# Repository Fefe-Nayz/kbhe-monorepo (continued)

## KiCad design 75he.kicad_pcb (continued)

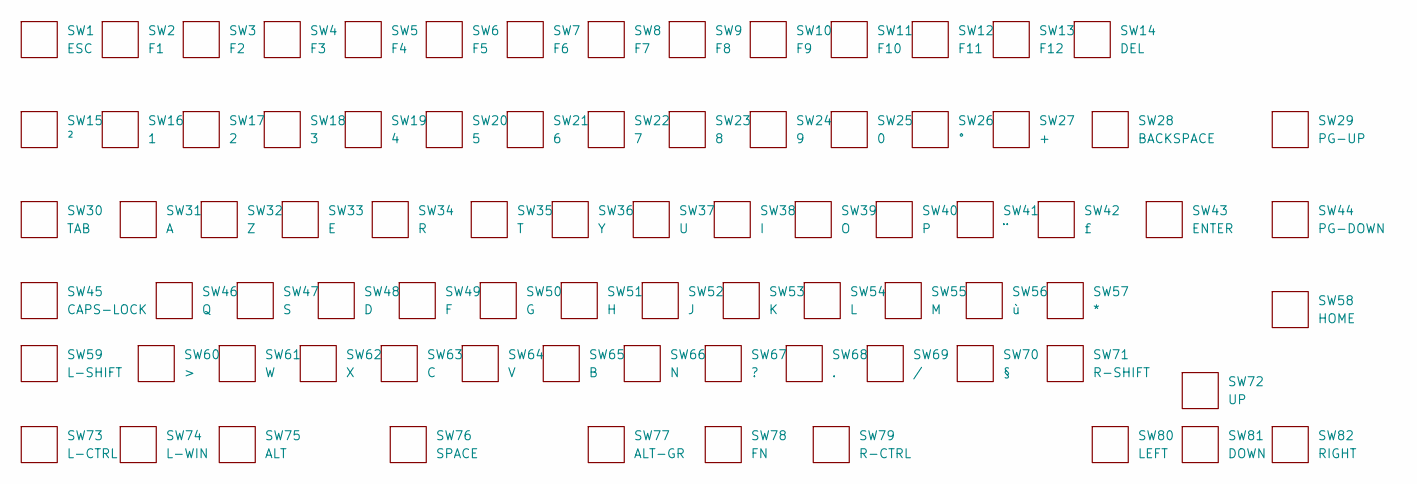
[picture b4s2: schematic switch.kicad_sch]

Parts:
SW1: ESC; Switch_1U
SW2: F1; Switch_1U
SW3: F2; Switch_1U
SW4: F3; Switch_1U
SW5: F4; Switch_1U
SW6: F5; Switch_1U
SW7: F6; Switch_1U
SW8: F7; Switch_1U
SW9: F8; Switch_1U
SW10: F9; Switch_1U
SW11: F10; Switch_1U
SW12: F11; Switch_1U
SW13: F12; Switch_1U
SW14: DEL; Switch_1U
SW15: ²; Switch_1U
SW16: 1; Switch_1U
SW17: 2; Switch_1U
SW18: 3; Switch_1U
SW19: 4; Switch_1U
SW20: 5; Switch_1U
SW21: 6; Switch_1U
SW22: 7; Switch_1U
SW23: 8; Switch_1U
SW24: 9; Switch_1U
SW25: 0; Switch_1U
SW26: °; Switch_1U
SW27: +; Switch_1U
SW28: BACKSPACE; Switch_2U
SW29: PG-UP; Switch_1U
SW30: TAB; Switch_1.5U
SW31: A; Switch_1U
SW32: Z; Switch_1U
SW33: E; Switch_1U
SW34: R; Switch_1U
SW35: T; Switch_1U
SW36: Y; Switch_1U
SW37: U; Switch_1U
SW38: I; Switch_1U
SW39: O; Switch_1U
SW40: P; Switch_1U
SW41: ¨; Switch_1U
SW42: £; Switch_1U
SW43: ENTER; Switch_ENTER_ISO
SW44: PG-DOWN; Switch_1U
SW45: CAPS-LOCK; Switch_1.75U
SW46: Q; Switch_1U
SW47: S; Switch_1U
SW48: D; Switch_1U
SW49: F; Switch_1U
SW50: G; Switch_1U
SW51: H; Switch_1U
SW52: J; Switch_1U
SW53: K; Switch_1U
SW54: L; Switch_1U
SW55: M; Switch_1U
SW56: ù; Switch_1U
SW57: *; Switch_1U
SW58: HOME; Switch_1U
SW59: L-SHIFT; Switch_1.25U
SW60: >; Switch_1U
SW61: W; Switch_1U
SW62: X; Switch_1U
SW63: C; Switch_1U
SW64: V; Switch_1U
SW65: B; Switch_1U
SW66: N; Switch_1U
SW67: ?; Switch_1U
SW68: .; Switch_1U
SW69: /; Switch_1U
SW70: §; Switch_1U
SW71: R-SHIFT; Switch_1.75U
SW72: UP; Switch_1U
SW73: L-CTRL; Switch_1.25U
SW74: L-WIN; Switch_1.25U
SW75: ALT; Switch_1.25U
SW76: SPACE; Switch_6.25U
SW77: ALT-GR; Switch_1U
SW78: FN; Switch_1U
SW79: R-CTRL; Switch_1U
SW80: LEFT; Switch_1U
SW81: DOWN; Switch_1U
SW82: RIGHT; Switch_1U

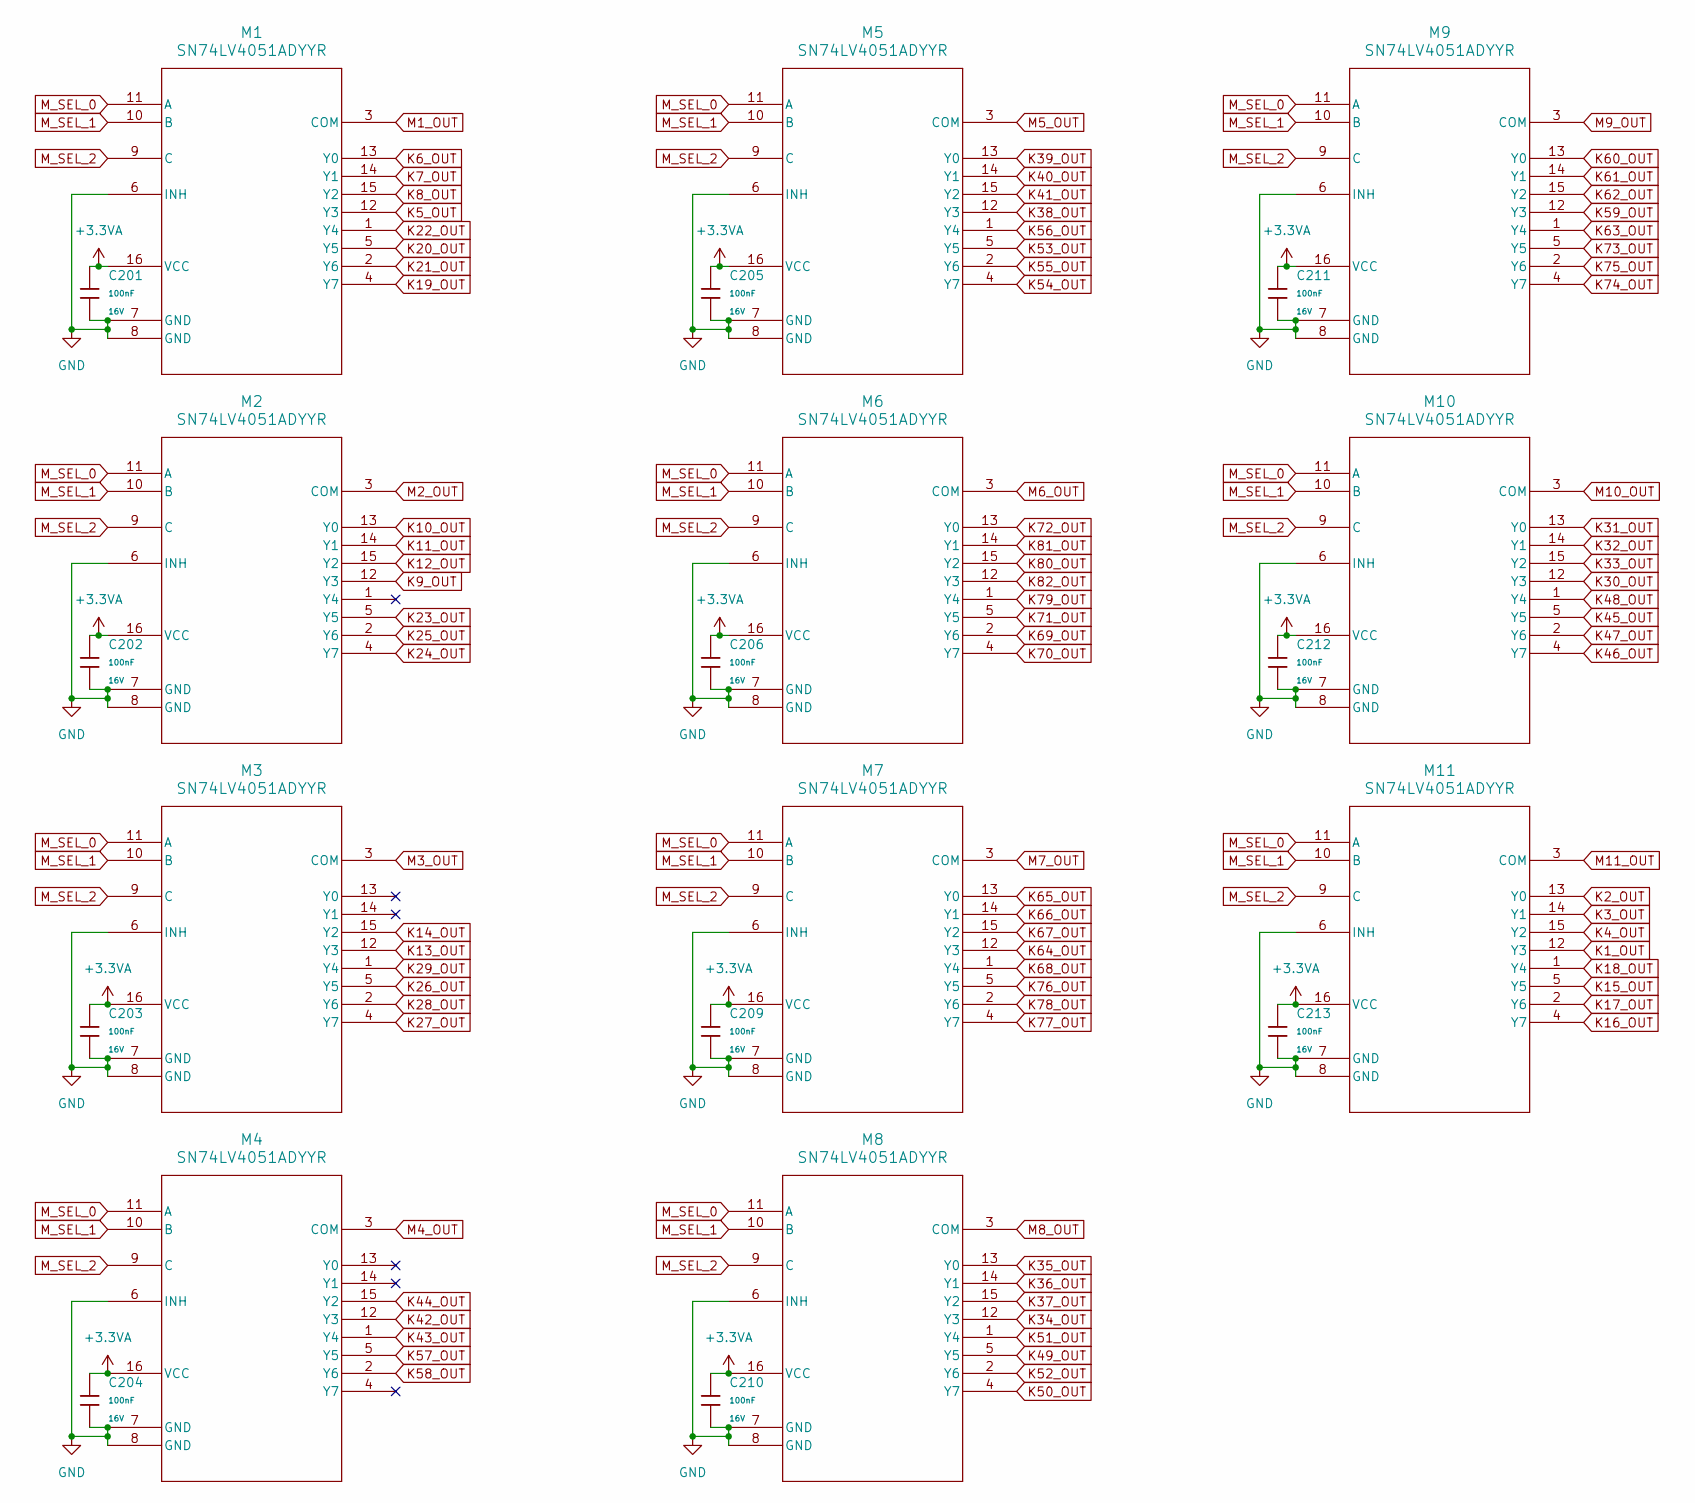
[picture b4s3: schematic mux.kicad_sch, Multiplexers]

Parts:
C201, C202, C203, C204, C205, C206, C209, C210, C211, C212, C213: 100nF; C_0402; Voltage Rated 16V; Tolerance ±10%; Part CL05B104KO5NNNC; LCSC C1525
M1, M2, M3, M4, M5, M6, M7, M8, M9, M10, M11: SN74LV4051ADYYR; SOT-23-THIN16_DYY_TEX

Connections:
+3.3VA: C201.1, C202.1, C203.1, C204.1, C205.1, C206.1, C209.1, C210.1, C211.1, C212.1, C213.1, M1.16 (VCC), M2.16 (VCC), M3.16 (VCC), M4.16 (VCC), M5.16 (VCC), M6.16 (VCC), M7.16 (VCC), M8.16 (VCC), M9.16 (VCC), M10.16 (VCC), M11.16 (VCC); also elsewhere on the board
GND: C201.2, C202.2, C203.2, C204.2, C205.2, C206.2, C209.2, C210.2, C211.2, C212.2, C213.2, M1.6 (INH), M1.7 (GND), M1.8 (GND), M2.6 (INH), M2.7 (GND), M2.8 (GND), M3.6 (INH), M3.7 (GND), M3.8 (GND), M4.6 (INH), M4.7 (GND), M4.8 (GND), M5.6 (INH), M5.7 (GND), M5.8 (GND), M6.6 (INH), M6.7 (GND), M6.8 (GND), M7.6 (INH), M7.7 (GND), M7.8 (GND), M8.6 (INH), M8.7 (GND), M8.8 (GND), M9.6 (INH), M9.7 (GND), M9.8 (GND), M10.6 (INH), M10.7 (GND), M10.8 (GND), M11.6 (INH), M11.7 (GND), M11.8 (GND); also elsewhere on the board
K1_OUT: M11.12 (Y3); also elsewhere on the board
K2_OUT: M11.13 (Y0); also elsewhere on the board
K3_OUT: M11.14 (Y1); also elsewhere on the board
K4_OUT: M11.15 (Y2); also elsewhere on the board
K5_OUT: M1.12 (Y3); also elsewhere on the board
K6_OUT: M1.13 (Y0); also elsewhere on the board
K7_OUT: M1.14 (Y1); also elsewhere on the board
K8_OUT: M1.15 (Y2); also elsewhere on the board
K9_OUT: M2.12 (Y3); also elsewhere on the board
K10_OUT: M2.13 (Y0); also elsewhere on the board
K11_OUT: M2.14 (Y1); also elsewhere on the board
K12_OUT: M2.15 (Y2); also elsewhere on the board
K13_OUT: M3.12 (Y3); also elsewhere on the board
K14_OUT: M3.15 (Y2); also elsewhere on the board
K15_OUT: M11.5 (Y5); also elsewhere on the board
K16_OUT: M11.4 (Y7); also elsewhere on the board
K17_OUT: M11.2 (Y6); also elsewhere on the board
K18_OUT: M11.1 (Y4); also elsewhere on the board
K19_OUT: M1.4 (Y7); also elsewhere on the board
K20_OUT: M1.5 (Y5); also elsewhere on the board
K21_OUT: M1.2 (Y6); also elsewhere on the board
K22_OUT: M1.1 (Y4); also elsewhere on the board
K23_OUT: M2.5 (Y5); also elsewhere on the board
K24_OUT: M2.4 (Y7); also elsewhere on the board
K25_OUT: M2.2 (Y6); also elsewhere on the board
K26_OUT: M3.5 (Y5); also elsewhere on the board
K27_OUT: M3.4 (Y7); also elsewhere on the board
K28_OUT: M3.2 (Y6); also elsewhere on the board
K29_OUT: M3.1 (Y4); also elsewhere on the board
K30_OUT: M10.12 (Y3); also elsewhere on the board
K31_OUT: M10.13 (Y0); also elsewhere on the board
K32_OUT: M10.14 (Y1); also elsewhere on the board
K33_OUT: M10.15 (Y2); also elsewhere on the board
K34_OUT: M8.12 (Y3); also elsewhere on the board
K35_OUT: M8.13 (Y0); also elsewhere on the board
K36_OUT: M8.14 (Y1); also elsewhere on the board
K37_OUT: M8.15 (Y2); also elsewhere on the board
K38_OUT: M5.12 (Y3); also elsewhere on the board
K39_OUT: M5.13 (Y0); also elsewhere on the board
K40_OUT: M5.14 (Y1); also elsewhere on the board
K41_OUT: M5.15 (Y2); also elsewhere on the board
K42_OUT: M4.12 (Y3); also elsewhere on the board
K43_OUT: M4.1 (Y4); also elsewhere on the board
K44_OUT: M4.15 (Y2); also elsewhere on the board
K45_OUT: M10.5 (Y5); also elsewhere on the board
K46_OUT: M10.4 (Y7); also elsewhere on the board
K47_OUT: M10.2 (Y6); also elsewhere on the board
K48_OUT: M10.1 (Y4); also elsewhere on the board
K49_OUT: M8.5 (Y5); also elsewhere on the board
K50_OUT: M8.4 (Y7); also elsewhere on the board
K51_OUT: M8.1 (Y4); also elsewhere on the board
K52_OUT: M8.2 (Y6); also elsewhere on the board
K53_OUT: M5.5 (Y5); also elsewhere on the board
K54_OUT: M5.4 (Y7); also elsewhere on the board
K55_OUT: M5.2 (Y6); also elsewhere on the board
K56_OUT: M5.1 (Y4); also elsewhere on the board
K57_OUT: M4.5 (Y5); also elsewhere on the board
K58_OUT: M4.2 (Y6); also elsewhere on the board
K59_OUT: M9.12 (Y3); also elsewhere on the board
K60_OUT: M9.13 (Y0); also elsewhere on the board
K61_OUT: M9.14 (Y1); also elsewhere on the board
K62_OUT: M9.15 (Y2); also elsewhere on the board
K63_OUT: M9.1 (Y4); also elsewhere on the board
K64_OUT: M7.12 (Y3); also elsewhere on the board
K65_OUT: M7.13 (Y0); also elsewhere on the board
K66_OUT: M7.14 (Y1); also elsewhere on the board
K67_OUT: M7.15 (Y2); also elsewhere on the board
K68_OUT: M7.1 (Y4); also elsewhere on the board
K69_OUT: M6.2 (Y6); also elsewhere on the board
K70_OUT: M6.4 (Y7); also elsewhere on the board
K71_OUT: M6.5 (Y5); also elsewhere on the board
K72_OUT: M6.13 (Y0); also elsewhere on the board
K73_OUT: M9.5 (Y5); also elsewhere on the board
K74_OUT: M9.4 (Y7); also elsewhere on the board
K75_OUT: M9.2 (Y6); also elsewhere on the board
K76_OUT: M7.5 (Y5); also elsewhere on the board
K77_OUT: M7.4 (Y7); also elsewhere on the board
K78_OUT: M7.2 (Y6); also elsewhere on the board
K79_OUT: M6.1 (Y4); also elsewhere on the board
K80_OUT: M6.15 (Y2); also elsewhere on the board
K81_OUT: M6.14 (Y1); also elsewhere on the board
K82_OUT: M6.12 (Y3); also elsewhere on the board
M1_OUT: M1.3 (COM); also elsewhere on the board
M2_OUT: M2.3 (COM); also elsewhere on the board
M3_OUT: M3.3 (COM); also elsewhere on the board
M4_OUT: M4.3 (COM); also elsewhere on the board
M5_OUT: M5.3 (COM); also elsewhere on the board
M6_OUT: M6.3 (COM); also elsewhere on the board
M7_OUT: M7.3 (COM); also elsewhere on the board
M8_OUT: M8.3 (COM); also elsewhere on the board
M9_OUT: M9.3 (COM); also elsewhere on the board
M10_OUT: M10.3 (COM); also elsewhere on the board
M11_OUT: M11.3 (COM); also elsewhere on the board
M_SEL_0: M1.11 (A), M2.11 (A), M3.11 (A), M4.11 (A), M5.11 (A), M6.11 (A), M7.11 (A), M8.11 (A), M9.11 (A), M10.11 (A), M11.11 (A); also elsewhere on the board
M_SEL_1: M1.10 (B), M2.10 (B), M3.10 (B), M4.10 (B), M5.10 (B), M6.10 (B), M7.10 (B), M8.10 (B), M9.10 (B), M10.10 (B), M11.10 (B); also elsewhere on the board
M_SEL_2: M1.9 (C), M2.9 (C), M3.9 (C), M4.9 (C), M5.9 (C), M6.9 (C), M7.9 (C), M8.9 (C), M9.9 (C), M10.9 (C), M11.9 (C); also elsewhere on the board

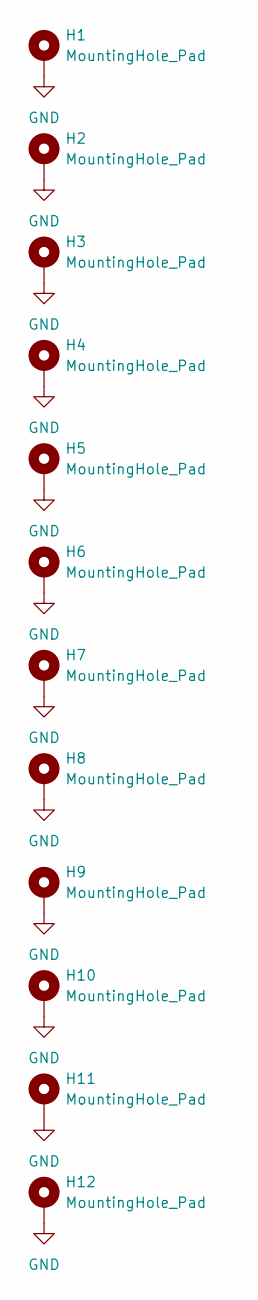
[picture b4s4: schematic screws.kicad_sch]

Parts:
H1, H2, H3, H4, H5, H6, H7, H8, H9, H10, H11, H12: MountingHole_Pad; MountingHole_2.2mm_M2_ISO14580_Pad

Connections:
GND: H1.1, H2.1, H3.1, H4.1, H5.1, H6.1, H7.1, H8.1, H9.1, H10.1, H11.1, H12.1; also elsewhere on the board

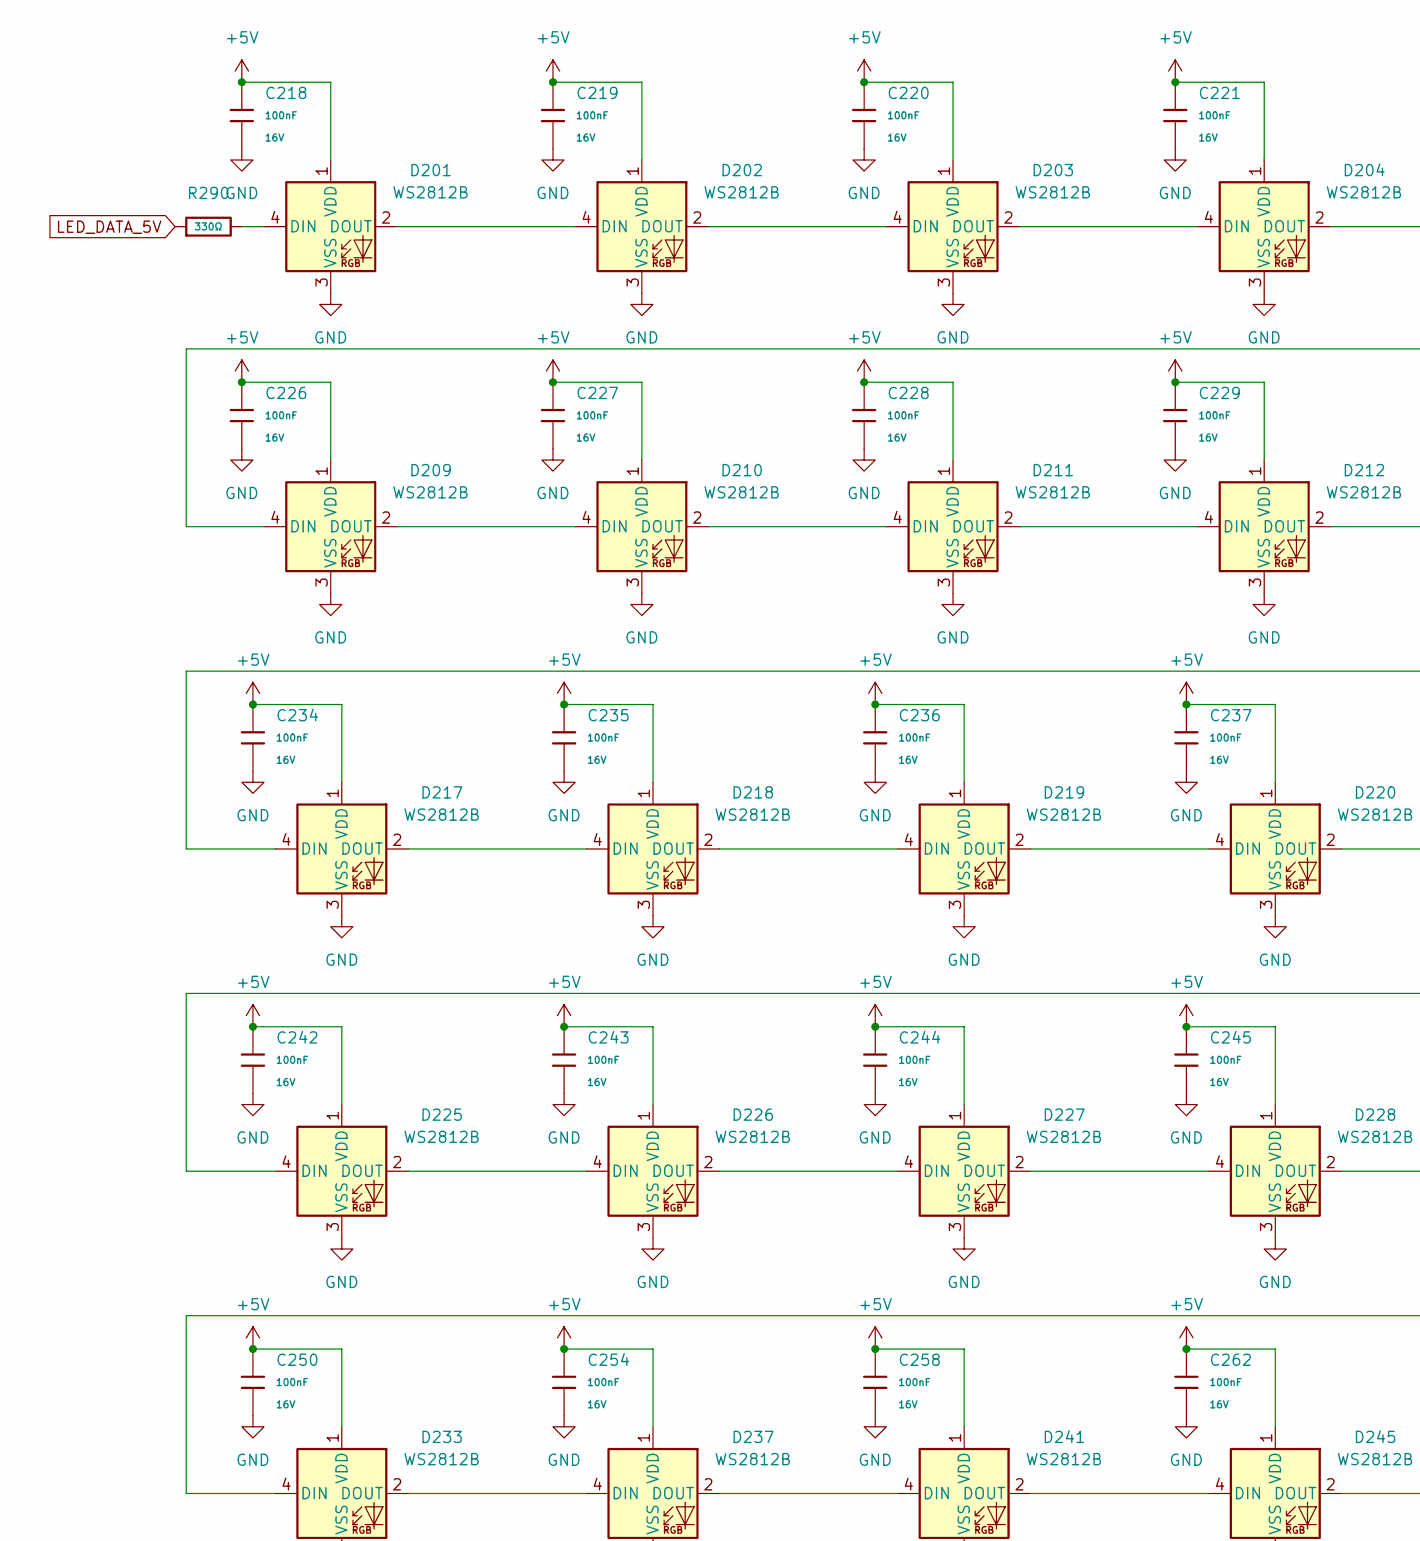
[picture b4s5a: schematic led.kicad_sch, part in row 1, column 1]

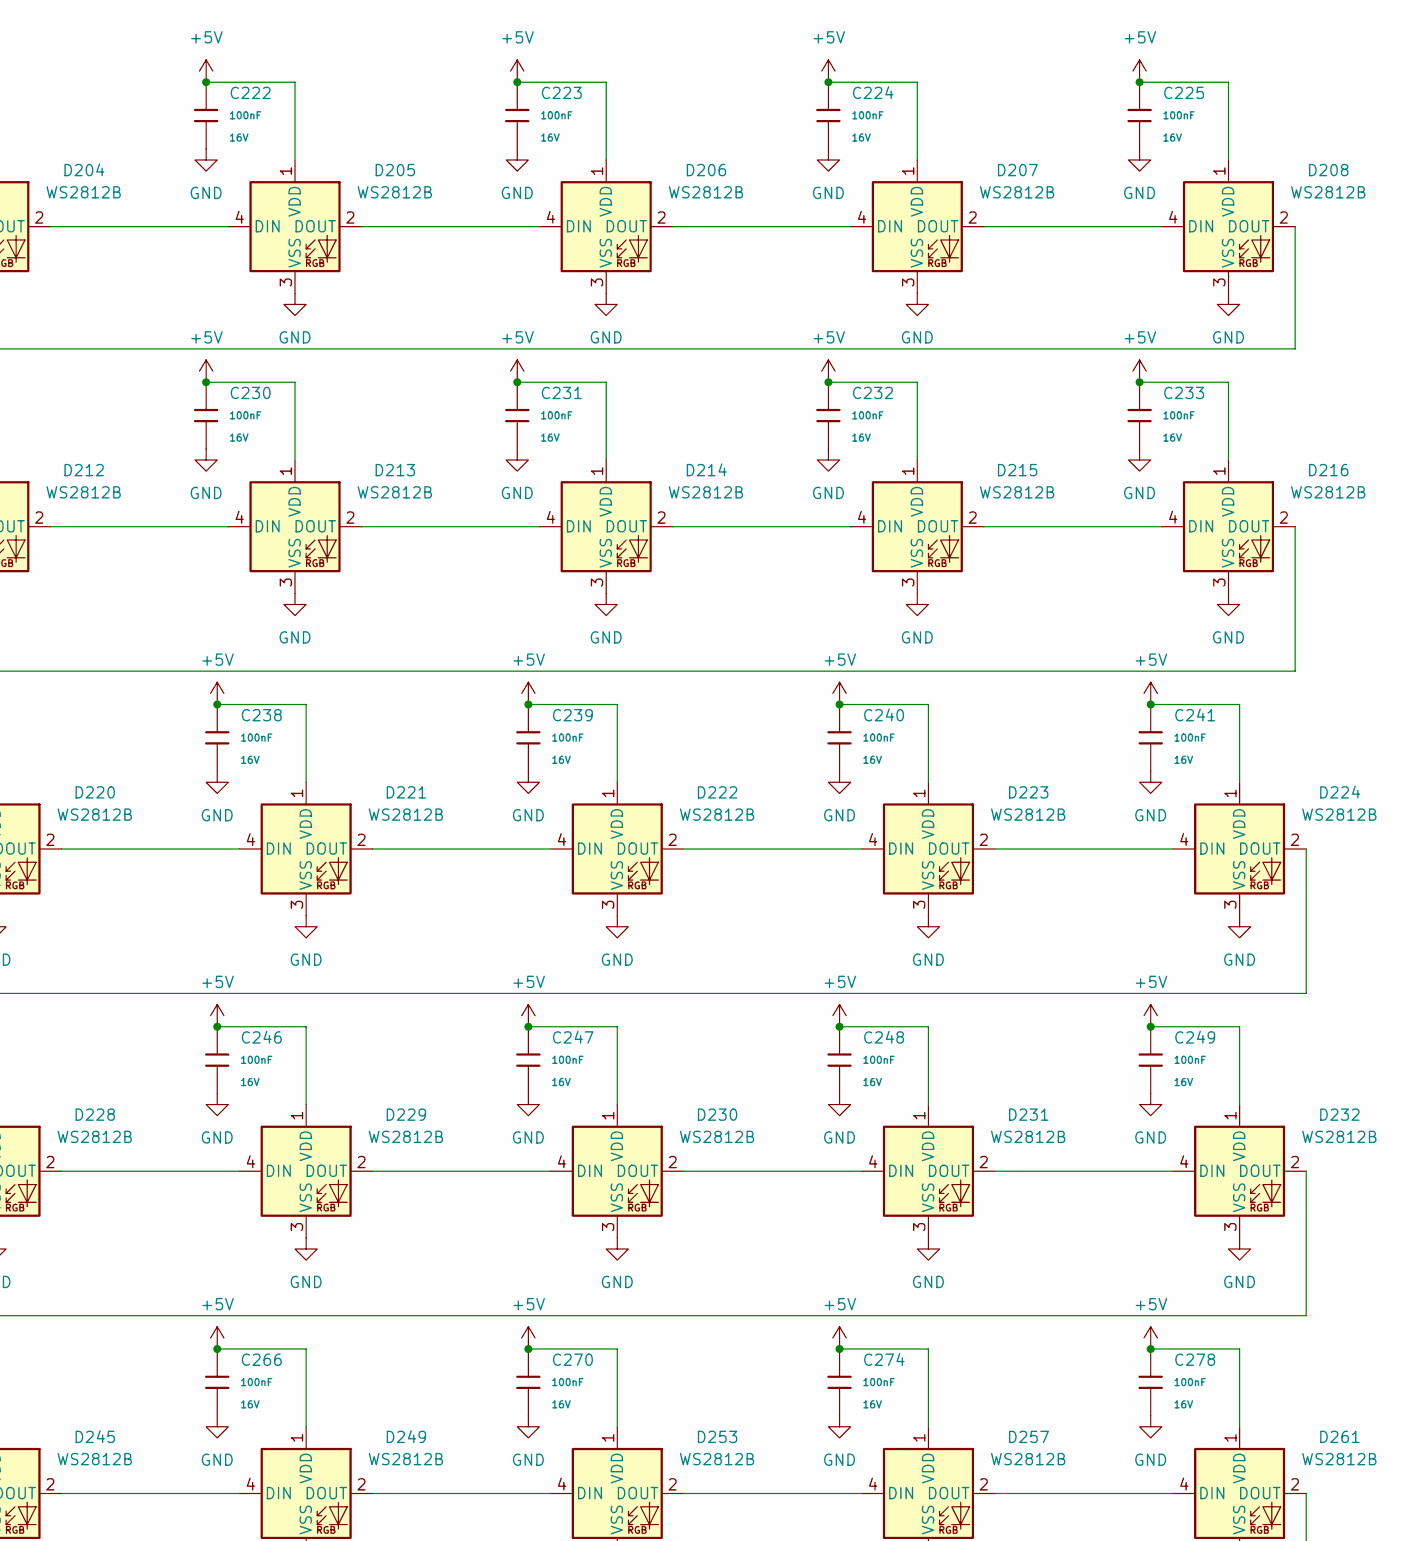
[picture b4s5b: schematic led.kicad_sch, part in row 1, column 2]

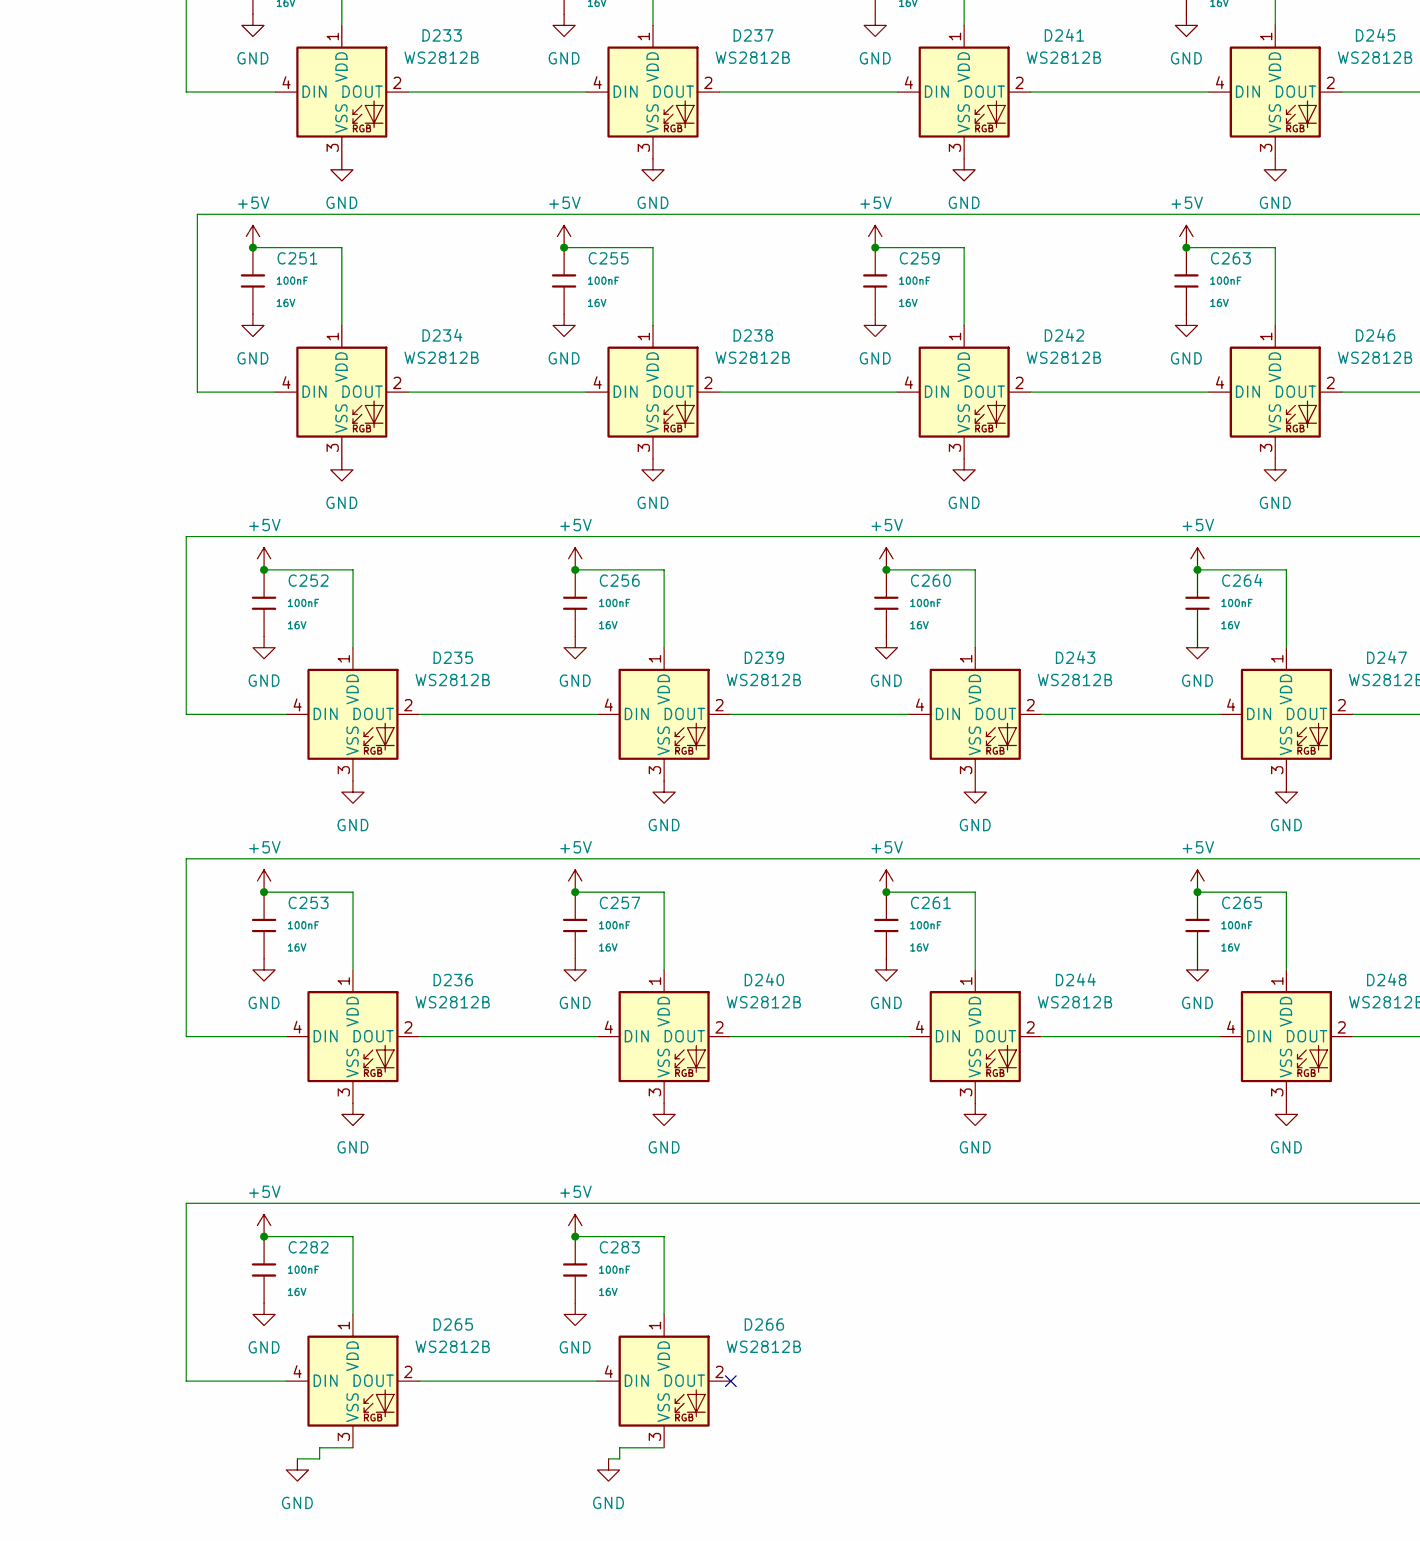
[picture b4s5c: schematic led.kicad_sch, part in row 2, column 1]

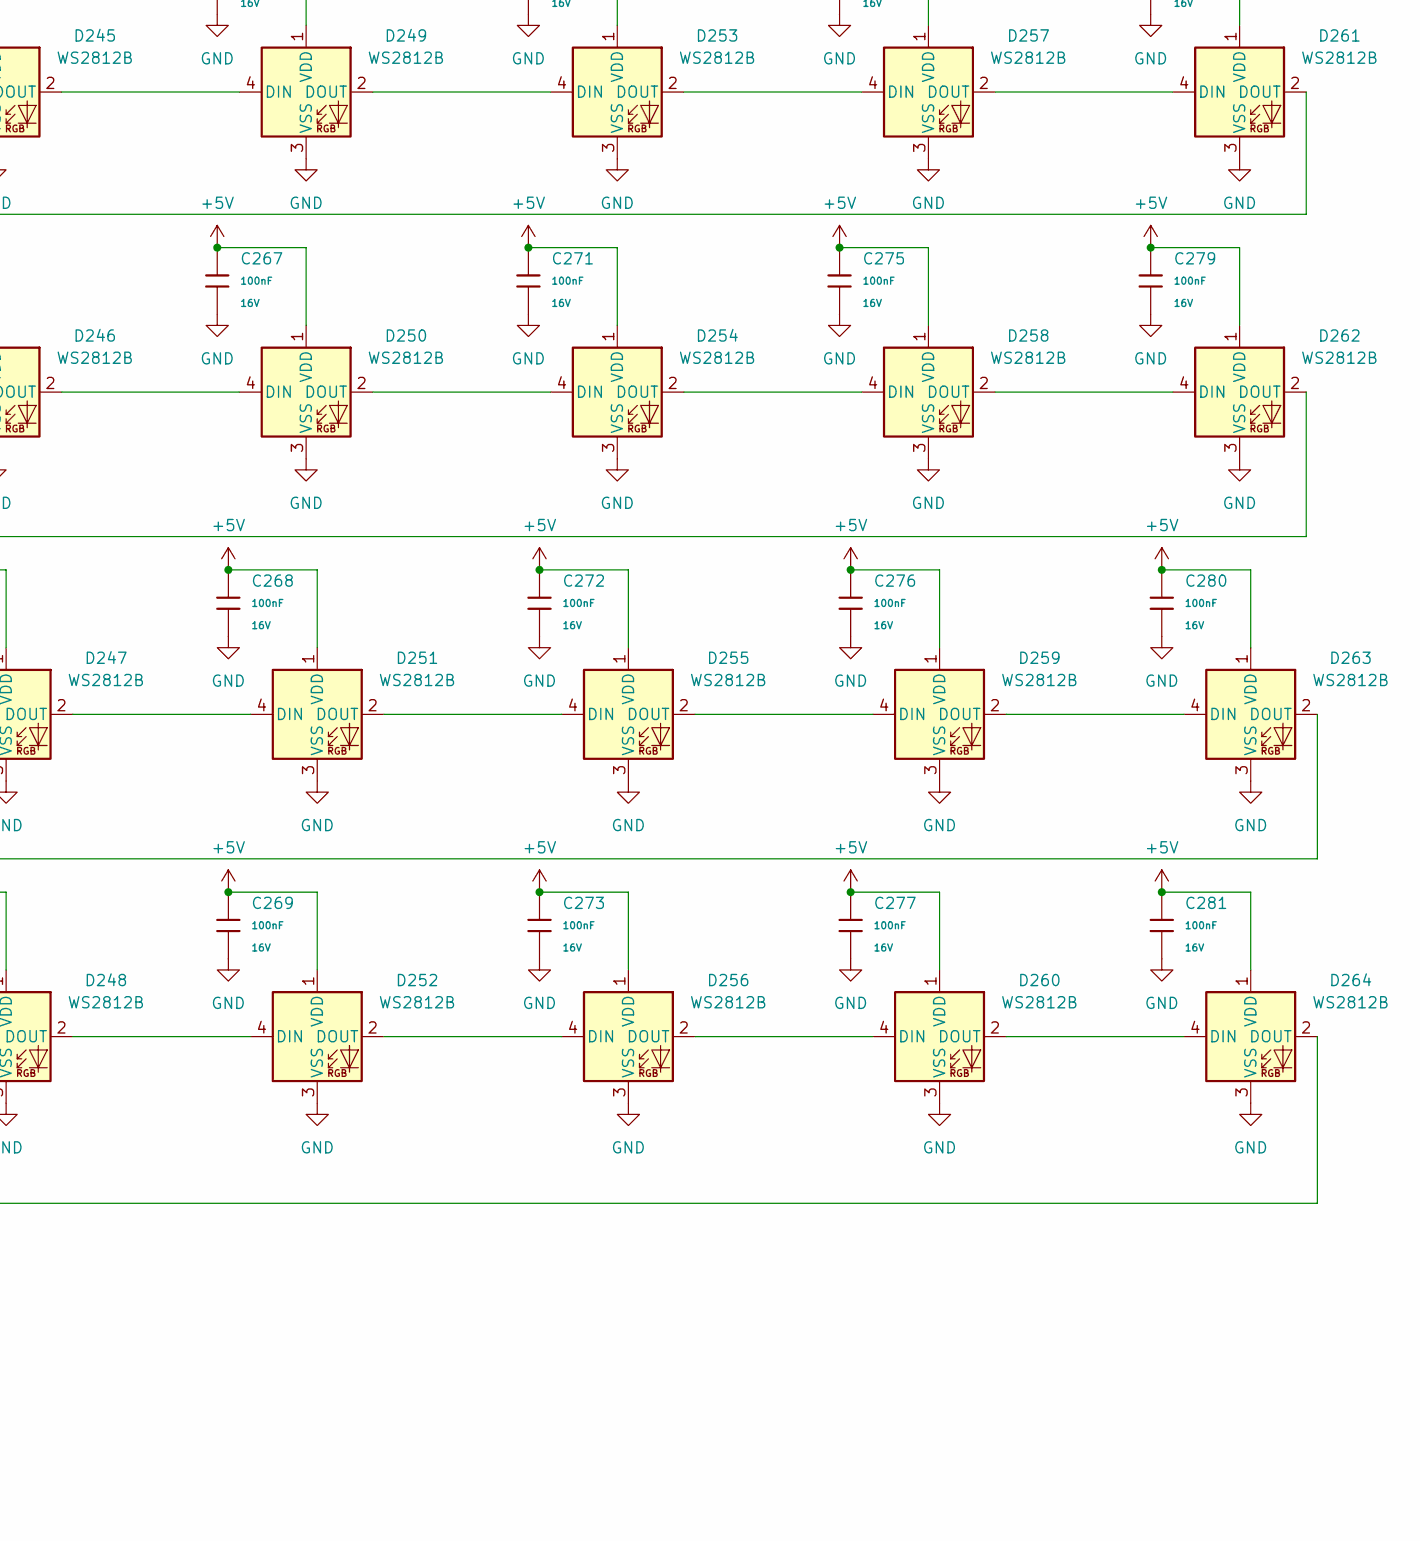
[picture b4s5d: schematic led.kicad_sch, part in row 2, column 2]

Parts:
C218, C219, C220, C221, C222, C223, C224, C225, C226, C227, C228, C229, C230, C231, C232, C233, C234, C235, C236, C237, C238, C239, C240, C241, C242, C243, C244, C245, C246, C247, C248, C249, C250, C251, C252, C253, C254, C255, C256, C257, C258, C259, C260, C261, C262, C263, C264, C265, C266, C267, C268, C269, C270, C271, C272, C273, C274, C275, C276, C277, C278, C279, C280, C281, C282, C283: 100nF; C_0402; Voltage Rated 16V; Tolerance ±10%; Part CL05B104KO5NNNC; LCSC C1525
D201, D202, D203, D204, D205, D206, D207, D208, D209, D210, D211, D212, D213, D214, D215, D216, D217, D218, D219, D220, D221, D222, D223, D224, D225, D226, D227, D228, D229, D230, D231, D232, D233, D234, D235, D236, D237, D238, D239, D240, D241, D242, D243, D244, D245, D246, D247, D248, D249, D250, D251, D252, D253, D254, D255, D256, D257, D258, D259, D260, D261, D262, D263, D264, D265, D266: WS2812B; LED_WS2812B_PLCC4_5.0x5.0mm_P3.2mm; LCSC C22461793
R290: 330Ω; R_0603; Overload Voltage (Max) 75V; Tolerance ±1%; Part 0603WAF3300T5E; LCSC C23138

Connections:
+5V: C218.1, C219.1, C220.1, C221.1, C222.1, C223.1, C224.1, C225.1, C226.1, C227.1, C228.1, C229.1, C230.1, C231.1, C232.1, C233.1, C234.1, C235.1, C236.1, C237.1, C238.1, C239.1, C240.1, C241.1, C242.1, C243.1, C244.1, C245.1, C246.1, C247.1, C248.1, C249.1, C250.1, C251.1, C252.1, C253.1, C254.1, C255.1, C256.1, C257.1, C258.1, C259.1, C260.1, C261.1, C262.1, C263.1, C264.1, C265.1, C266.1, C267.1, C268.1, C269.1, C270.1, C271.1, C272.1, C273.1, C274.1, C275.1, C276.1, C277.1, C278.1, C279.1, C280.1, C281.1, C282.1, C283.1, D201.1 (VDD), D202.1 (VDD), D203.1 (VDD), D204.1 (VDD), D205.1 (VDD), D206.1 (VDD), D207.1 (VDD), D208.1 (VDD), D209.1 (VDD), D210.1 (VDD), D211.1 (VDD), D212.1 (VDD), D213.1 (VDD), D214.1 (VDD), D215.1 (VDD), D216.1 (VDD), D217.1 (VDD), D218.1 (VDD), D219.1 (VDD), D220.1 (VDD), D221.1 (VDD), D222.1 (VDD), D223.1 (VDD), D224.1 (VDD), D225.1 (VDD), D226.1 (VDD), D227.1 (VDD), D228.1 (VDD), D229.1 (VDD), D230.1 (VDD), D231.1 (VDD), D232.1 (VDD), D233.1 (VDD), D234.1 (VDD), D235.1 (VDD), D236.1 (VDD), D237.1 (VDD), D238.1 (VDD), D239.1 (VDD), D240.1 (VDD), D241.1 (VDD), D242.1 (VDD), D243.1 (VDD), D244.1 (VDD), D245.1 (VDD), D246.1 (VDD), D247.1 (VDD), D248.1 (VDD), D249.1 (VDD), D250.1 (VDD), D251.1 (VDD), D252.1 (VDD), D253.1 (VDD), D254.1 (VDD), D255.1 (VDD), D256.1 (VDD), D257.1 (VDD), D258.1 (VDD), D259.1 (VDD), D260.1 (VDD), D261.1 (VDD), D262.1 (VDD), D263.1 (VDD), D264.1 (VDD), D265.1 (VDD), D266.1 (VDD); also elsewhere on the board
GND: C218.2, C219.2, C220.2, C221.2, C222.2, C223.2, C224.2, C225.2, C226.2, C227.2, C228.2, C229.2, C230.2, C231.2, C232.2, C233.2, C234.2, C235.2, C236.2, C237.2, C238.2, C239.2, C240.2, C241.2, C242.2, C243.2, C244.2, C245.2, C246.2, C247.2, C248.2, C249.2, C250.2, C251.2, C252.2, C253.2, C254.2, C255.2, C256.2, C257.2, C258.2, C259.2, C260.2, C261.2, C262.2, C263.2, C264.2, C265.2, C266.2, C267.2, C268.2, C269.2, C270.2, C271.2, C272.2, C273.2, C274.2, C275.2, C276.2, C277.2, C278.2, C279.2, C280.2, C281.2, C282.2, C283.2, D201.3 (VSS), D202.3 (VSS), D203.3 (VSS), D204.3 (VSS), D205.3 (VSS), D206.3 (VSS), D207.3 (VSS), D208.3 (VSS), D209.3 (VSS), D210.3 (VSS), D211.3 (VSS), D212.3 (VSS), D213.3 (VSS), D214.3 (VSS), D215.3 (VSS), D216.3 (VSS), D217.3 (VSS), D218.3 (VSS), D219.3 (VSS), D220.3 (VSS), D221.3 (VSS), D222.3 (VSS), D223.3 (VSS), D224.3 (VSS), D225.3 (VSS), D226.3 (VSS), D227.3 (VSS), D228.3 (VSS), D229.3 (VSS), D230.3 (VSS), D231.3 (VSS), D232.3 (VSS), D233.3 (VSS), D234.3 (VSS), D235.3 (VSS), D236.3 (VSS), D237.3 (VSS), D238.3 (VSS), D239.3 (VSS), D240.3 (VSS), D241.3 (VSS), D242.3 (VSS), D243.3 (VSS), D244.3 (VSS), D245.3 (VSS), D246.3 (VSS), D247.3 (VSS), D248.3 (VSS), D249.3 (VSS), D250.3 (VSS), D251.3 (VSS), D252.3 (VSS), D253.3 (VSS), D254.3 (VSS), D255.3 (VSS), D256.3 (VSS), D257.3 (VSS), D258.3 (VSS), D259.3 (VSS), D260.3 (VSS), D261.3 (VSS), D262.3 (VSS), D263.3 (VSS), D264.3 (VSS), D265.3 (VSS), D266.3 (VSS); also elsewhere on the board
LED_DATA_5V: R290.1
unnamed: D201.4 (DIN), R290.2
unnamed: D201.2 (DOUT), D202.4 (DIN)
unnamed: D202.2 (DOUT), D203.4 (DIN)
unnamed: D203.2 (DOUT), D204.4 (DIN)
unnamed: D204.2 (DOUT), D205.4 (DIN)
unnamed: D205.2 (DOUT), D206.4 (DIN)
unnamed: D206.2 (DOUT), D207.4 (DIN)
unnamed: D207.2 (DOUT), D208.4 (DIN)
unnamed: D208.2 (DOUT), D209.4 (DIN)
unnamed: D209.2 (DOUT), D210.4 (DIN)
unnamed: D210.2 (DOUT), D211.4 (DIN)
unnamed: D211.2 (DOUT), D212.4 (DIN)
unnamed: D212.2 (DOUT), D213.4 (DIN)
unnamed: D213.2 (DOUT), D214.4 (DIN)
unnamed: D214.2 (DOUT), D215.4 (DIN)
unnamed: D215.2 (DOUT), D216.4 (DIN)
unnamed: D216.2 (DOUT), D217.4 (DIN)
unnamed: D217.2 (DOUT), D218.4 (DIN)
unnamed: D218.2 (DOUT), D219.4 (DIN)
unnamed: D219.2 (DOUT), D220.4 (DIN)
unnamed: D220.2 (DOUT), D221.4 (DIN)
unnamed: D221.2 (DOUT), D222.4 (DIN)
unnamed: D222.2 (DOUT), D223.4 (DIN)
unnamed: D223.2 (DOUT), D224.4 (DIN)
unnamed: D224.2 (DOUT), D225.4 (DIN)
unnamed: D225.2 (DOUT), D226.4 (DIN)
unnamed: D226.2 (DOUT), D227.4 (DIN)
unnamed: D227.2 (DOUT), D228.4 (DIN)
unnamed: D228.2 (DOUT), D229.4 (DIN)
unnamed: D229.2 (DOUT), D230.4 (DIN)
unnamed: D230.2 (DOUT), D231.4 (DIN)
unnamed: D231.2 (DOUT), D232.4 (DIN)
unnamed: D232.2 (DOUT), D233.4 (DIN)
unnamed: D233.2 (DOUT), D237.4 (DIN)
unnamed: D234.4 (DIN), D261.2 (DOUT)
unnamed: D234.2 (DOUT), D238.4 (DIN)
unnamed: D235.4 (DIN), D262.2 (DOUT)
unnamed: D235.2 (DOUT), D239.4 (DIN)
unnamed: D236.4 (DIN), D263.2 (DOUT)
unnamed: D236.2 (DOUT), D240.4 (DIN)
unnamed: D237.2 (DOUT), D241.4 (DIN)
unnamed: D238.2 (DOUT), D242.4 (DIN)
unnamed: D239.2 (DOUT), D243.4 (DIN)
unnamed: D240.2 (DOUT), D244.4 (DIN)
unnamed: D241.2 (DOUT), D245.4 (DIN)
unnamed: D242.2 (DOUT), D246.4 (DIN)
unnamed: D243.2 (DOUT), D247.4 (DIN)
unnamed: D244.2 (DOUT), D248.4 (DIN)
unnamed: D245.2 (DOUT), D249.4 (DIN)
unnamed: D246.2 (DOUT), D250.4 (DIN)
unnamed: D247.2 (DOUT), D251.4 (DIN)
unnamed: D248.2 (DOUT), D252.4 (DIN)
unnamed: D249.2 (DOUT), D253.4 (DIN)
unnamed: D250.2 (DOUT), D254.4 (DIN)
unnamed: D251.2 (DOUT), D255.4 (DIN)
unnamed: D252.2 (DOUT), D256.4 (DIN)
unnamed: D253.2 (DOUT), D257.4 (DIN)
unnamed: D254.2 (DOUT), D258.4 (DIN)
unnamed: D255.2 (DOUT), D259.4 (DIN)
unnamed: D256.2 (DOUT), D260.4 (DIN)
unnamed: D257.2 (DOUT), D261.4 (DIN)
unnamed: D258.2 (DOUT), D262.4 (DIN)
unnamed: D259.2 (DOUT), D263.4 (DIN)
unnamed: D260.2 (DOUT), D264.4 (DIN)
unnamed: D264.2 (DOUT), D265.4 (DIN)
unnamed: D265.2 (DOUT), D266.4 (DIN)
